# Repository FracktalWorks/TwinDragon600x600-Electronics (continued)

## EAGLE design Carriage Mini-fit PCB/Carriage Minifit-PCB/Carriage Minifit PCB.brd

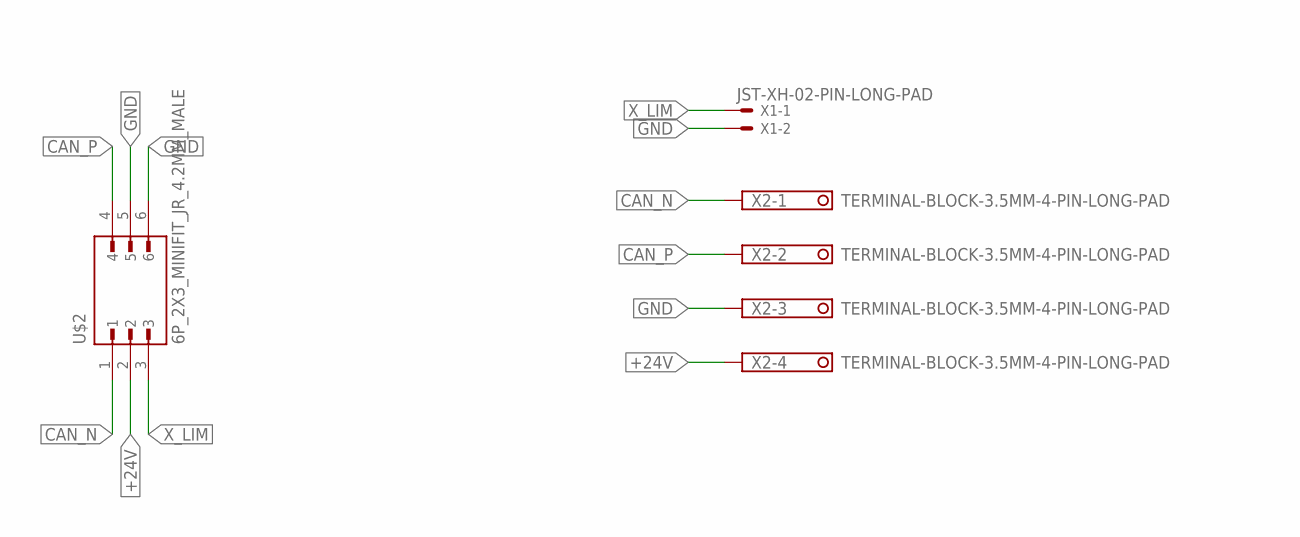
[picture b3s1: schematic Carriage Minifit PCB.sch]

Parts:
U$2: 6P_2X3_MINIFIT_JR_4.2MM_MALE
X1: JST-XH-02-PIN-LONG-PAD; JST-XH-02-PACKAGE-LONG-PAD
X2: TERMINAL-BLOCK-3.5MM-4-PIN-LONG-PAD; TERMINAL-BLOCK-4-PIN-3.5MM-LONG-PAD

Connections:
+24V: U$2.2, X2.4
CAN_N: U$2.1, X2.1
CAN_P: U$2.4, X2.2
GND: U$2.5, U$2.6, X1.2, X2.3
X_LIM: U$2.3, X1.1

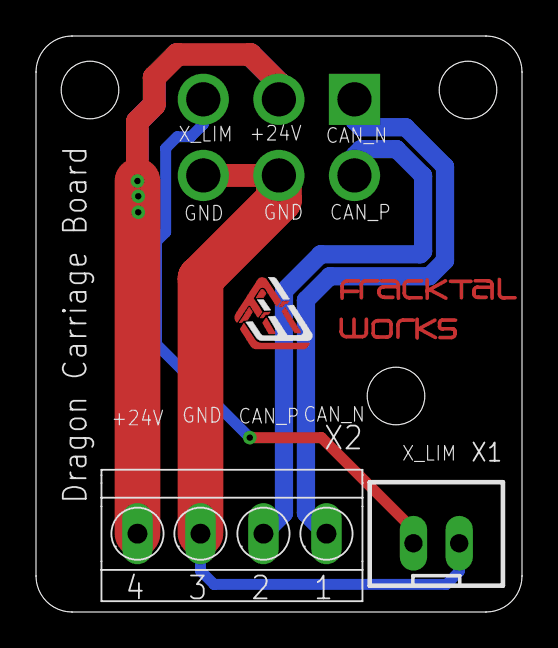
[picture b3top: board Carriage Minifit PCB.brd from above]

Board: 2 copper layers, 27.0 x 32.0 mm, 4 parts (1 on the bottom side), 5 nets.

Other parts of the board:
U$1: FWLOGO_SMALL_FOOTPRINT; FWLOGO_SMALL

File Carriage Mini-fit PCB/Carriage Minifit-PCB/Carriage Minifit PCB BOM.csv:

Qty,Designator,Footprint,Comment,LCSC Part #,Description,Value
1,J1,MOLEX_39281063,39281063,,Conn Wire to Board HDR 6Power POS 4.2mm Solder ST Top Entry Thru-Hole Mini-Fit Jr Bag  Check availability,39281063
1,X1,JST-XH-02-PACKAGE-LONG-PAD,JST-XH-02-PIN-LONG-PAD,,JST XH Connector 2 Pin,JST-XH-02-PIN-LONG-PAD
1,X2,TERMINAL-BLOCK-4-PIN-3.5MM-LONG-PAD,TERMINAL-BLOCK-3.5MM-4-PIN-LONG-PAD,,Terminal Block 3.5mm,TERMINAL-BLOCK-3.5MM-4-PIN-LONG-PAD

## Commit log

2024-03-20 Added datasheets, manuals and PCB files of relevant electronics used
2024-05-17 added CM4 shield board design files
2024-05-18 Design updates
2024-05-21 update to board design
2024-06-11 Correction of DRC check, and changes accordingly
